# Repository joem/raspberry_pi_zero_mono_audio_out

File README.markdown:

Raspberry Pi Zero Mono Audio Output
===================================

> :warning: _NOTE: This board hasn’t been tested yet. It’s simple enough that I’m fairly certain it’s OK, but in case it’s not, this is why. After I test it, I’ll remove this note._

There are already some other RPi Zero (or Zero W) audio output pcbs available, but this one was designed specifically with several goals in mind:

- mono
- through hole
- fits inside my RPi Zero case
- uses a PJ302M jack to mount it to the case
- decently documented

It’s based on [a circuit from tinkernut](http://www.tinkernut.com/2017/04/adding-audio-output-raspberry-pi-zero-tinkernut-workbench/) though I’m not sure if they originated it (it’s just a passive filter, after all). See that tinkernut page for more info about setting up the RPi to work with it. And if that page ever disappears, feel free to google for something like “rpi zero pwm audio” since there are many articles about how to set that up. I used through-hole components because I didn’t have all the right parts in SMD and it's small enough for my needs. There are no mounting holes because it’s intended to be panel-mounted via the jack.

This was designed as a KiCad project, but if you want to fabricate a PCB you don't need KiCad since the gerbers are in the gerbers folder. Also, there's a PDF schematic in the pdfs directory. And if you just want to order PCBs, [there's an OSHPark project](https://oshpark.com/shared_projects/ILTMx6KX).

Opening the KiCad project requires KiCad 6 at a minimum. I've removed the old KiCad 5 files.

BOM:

- R1 = 270R
- R2 = 150R
- C1 = 10uF electrolytic, 2.5mm lead spacing
- C2 = 33nF ceramic, 5mm lead spacing (tinkernut’s page says “0.33uF” but other similar schematics say 33nF)
- J1 = PJ302M 3.5mm mono jack
- J2 = 1x2 pin header (I use right angle)

The lead spacing for the capacitors is not a strict requirement, since you can always bend the leads in or out a bit if you’re close. When shopping for the electrolytic cap, be aware of its size, especially if you’re going to be putting this in a tight space like I am. (I prefer using the Panasonic ECE-A1VKS100 since it's nice and short. Mouser part #: 667-ECE-A1VKS100)

Render from KiCad:

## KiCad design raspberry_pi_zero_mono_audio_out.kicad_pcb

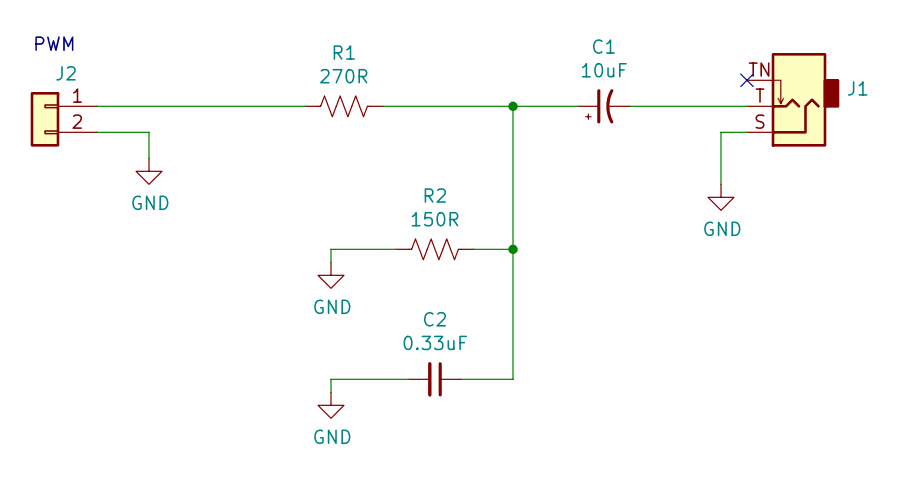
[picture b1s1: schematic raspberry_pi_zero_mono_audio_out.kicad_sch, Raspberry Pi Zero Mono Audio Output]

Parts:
C1: 10uF; CP_Radial_D5.0mm_P2.50mm
C2: 0.33uF; C_Disc_D5.0mm_W2.5mm_P5.00mm
J1: AudioJack2_SwitchT; Jack_3.5mm_QingPu_WQP-PJ302M_Horizontal
J2: Conn_01x02; PinHeader_1x02_P2.54mm_Vertical
R1: 270R; R_Axial_DIN0207_L6.3mm_D2.5mm_P7.62mm_Horizontal
R2: 150R; R_Axial_DIN0207_L6.3mm_D2.5mm_P7.62mm_Horizontal

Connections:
/PWM: J2.1, R1.2
GND: C2.2, J1.S, J2.2, R2.2
unnamed: C1.1, C2.1, R1.1, R2.1
unnamed: C1.2, J1.T

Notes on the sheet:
PWM

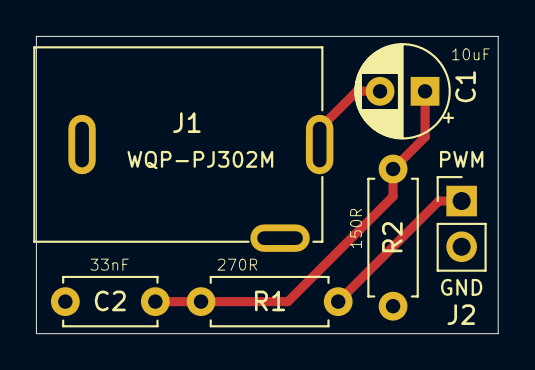
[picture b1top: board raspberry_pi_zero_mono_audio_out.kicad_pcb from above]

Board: 2 copper layers, 25.7 x 16.5 mm, 6 parts (0 on the bottom side), 4 nets.

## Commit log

2020-04-08 Add readme
2020-04-08 Update readme with missing part number
2020-04-08 Add rendered image to readme
2020-04-08 Update image in readme
2020-04-22 Update silkscreen with github URL
2023-04-02 Update project to kicad 6+
2023-04-02 Add .gitignore
